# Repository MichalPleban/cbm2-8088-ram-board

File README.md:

# CBM-II 8088 CPU + RAM expansion board

## About the project

This repository is the hardware part of the project to create a PC compatibility system for Commodore CBM-II computers. The software counterpart is located at:

https://github.com/MichalPleban/cbm2-pc-emulator

More information about the project can be found at:

http://www.cbm-ii.com/

## About the board

The board is a replica of the original 8088 processor board for Commodore CBM-II computers. The replica is 100% compatible with the original card, so you can still run original MS-DOS 1.25 or CP/M-86 1.1 on it.

Several additional features were added to the card which allow for building a system that has enough power to run modern versions of DOS and DOS software:

### Fixed stability problems

The original card has serious stability problems in many machines, and it simply refuses to run on most low-profile CBM-II computers. These problems are caused by noise on /ERAS and /ECAS signals which cause memory corruption. Depending on the computer motherboard and/or PLA, the card may either work without any problems, hang once every few minutes or simply not work at all.

These problems are removed in the replica, and it works in all CBM-II computers.

### 1 MB memory expansion

The expanded memory is visible to both CPUs and allows DOS to access full 640 kB of memory – running DOS in only 256 kB leaves too little room for almost any application. The 64 kB segments above the 640 kB barrier can be individually turned off to allow other hardware (such as ISA graphics cards) to map into the address space.

The card has also the cartridge ROM with “fast boot” KERNAL modifications, thanks to which the memory test during powerup is greatly shortened (the test of 1 MB memory with the original would take around 2 minutes – this is shortened to mere 4 seconds).

### 12 MHz system clock

The card is equipped with a clock generator that produces either 12 MHz system clock with 50% duty cycle (for the NEC V20 processor) or 8 MHz clock with 33% duty cycle (for the 8088 processor). Compared with the 5 MHz on the original card, it gives a much faster system.
The system speed is further increased by using SRAM chips, which do not require refresh. Therefore the memory refresh system does not steal cycles from the CPU like on the original card.

### Hardware SPI interface

The SPI system is used to create a fast interface to a SD card, which serves as a 8 GB hard disk. Because the interface is implemented in hardware using shift registers, in combination with the INS/OUTS instructions of the NEC V20 CPU, it allows for theoretical read and write speed exceeding 1 MB / s.

### Battery backed RTC clock

The clock keeps the date and time for DOS and has also a few bytes of battery backed NVRAM to hold persistent configuration data.

### Reprogrammable EEPROM

The PC compatibility software is stored in an EEPROM chip, which can be reprogrammed from the 8088 side. Thanks to this, The library can be upgraded just by putting a newer version on the SD card and running the upgrade program from within DOS.

Having the whole software in the EEPROM allows also for diskless boot – the whole software is loaded from ROM, not from the disk like with the original card.

### Expansion port

The expansion port contains all the CPU bus signals, which should make it possible to add an ISA interface in the future. A smaller port with just the SPI and I2C signals is also available for additional hardware expansions in the future.

### Support for hardware virtualization

The card can generate NMI signal whenever an I/O port is accessed by the 8088 CPU. The I/O port access and the value being written to it are stored in hardware latches, so that the NMI routine can determine which I/O port was accessed and perform appropriate actions to simulate the hardware.

A video memory access latch was also added, which holds information about which parts of the video buffer at segment 0B000h was modified. This information speeds up screen refresh, because only the modified parts are being refreshed.

### 8087 coprocessor compatibility
The original card had a bug, due to which using the 8087 FPU was not possible – the card would lock up when the FPU was inserted into its socket. This bug has been fixed in the replica.

### Unobtainable chips replaced

The original card uses the 6525 Tri-Port Interface chip which is impossible to obtain. It has been replaced by an 8255 chip.

### Cartridge ROM sockets
The card has sockets for cartridge ROM or RAM at $4000, $6000 and $C000 which allow using  existing cartridge images. If a cartridge ROM is present, the card boot menu allows selecting whether to boot into BASIC or start the cartridge.

## Building the card

The PCB of the board has 4 layers to make it smaller and fit into the small space inside the low-profile CBM-II machines. Check with your PCB factory if they can make a 4 layer PCB for you.

The board contains an Atmel ATF1508 CPLD chip. You need a suitable programmer, such as ATF15xx-DK2, to program the chip. The board has a JEDEC connector which can be used to connect to the programmer directly. Use the cobalt.jed file from the repository to program the chip.

There are two ROM images in the archive which are necessary for the card to work:
-	8088.bin – 27C512 chip image to be placed at U7D
-	6509.bin  - 27C64 chip image to be placed at U2C

There are also chargen_lp.bin and chargen_hp.bin images which can be used to replace the character ROM in your machine (correspondently for low-profile and high-profile machines). They contain an alternate character set with some characters that are useful when running DOS (such as the backspace character). The card must be configured to use this character set – press F10 after booting the card.

The freedos.zip archive contains an image of a bootable FreeDOS hard disk. Put this image onto an SD card that is at least 8 GB of size (there are several SD card imaging applications available, I am using Win32 Disk Imager). After writing the images, the SD card will be readable on your PC, so you can easily add other applications. Note that you must use this image to boot the 8088 card, because the SD card must be formatted with special geometry for the INT 13h functions in the 8088 BIOS.

The ROM image from the repository contains the current version of the PC compatibility library. If you want to update the library in the future, grab the upgrade.com file from the repository, put it on the SD card and run it in DOS – it will write the newest version to the EEPROM chip on the board.

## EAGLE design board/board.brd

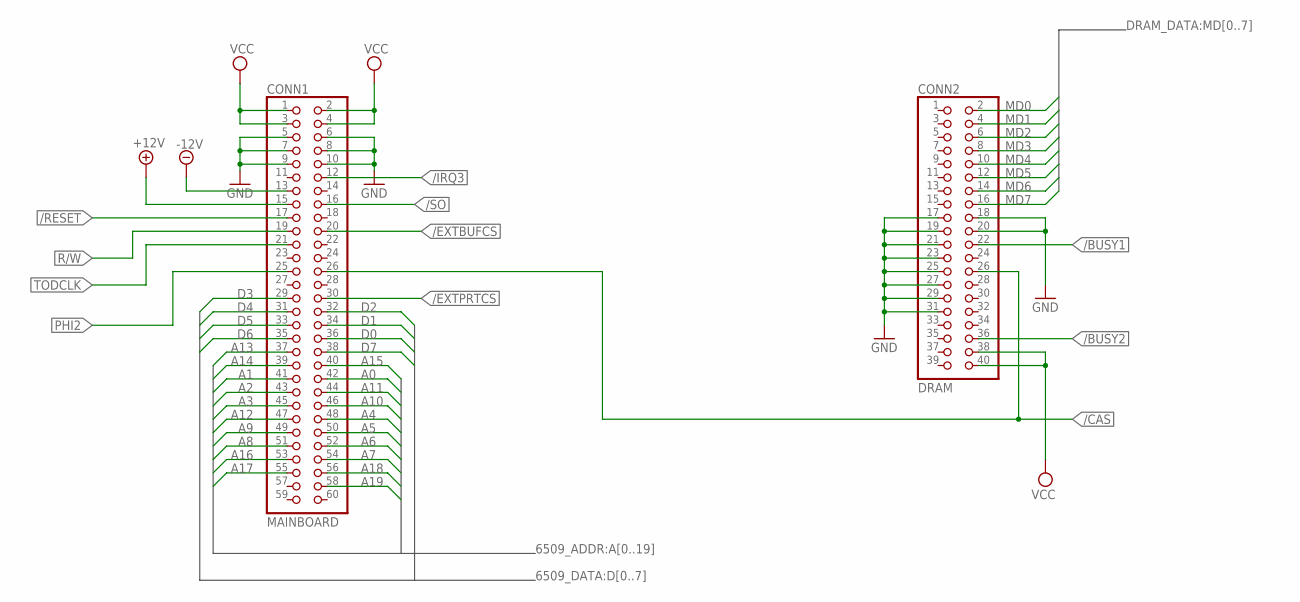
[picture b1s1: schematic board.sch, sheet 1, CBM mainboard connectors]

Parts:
CONN1: MAINBOARD; 2X30
CONN2: DRAM; 2X20

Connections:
+12V: CONN1.15; also elsewhere on the board
-12V: CONN1.13; also elsewhere on the board
/BUSY1: CONN2.22; also elsewhere on the board
/BUSY2: CONN2.36; also elsewhere on the board
/CAS: CONN1.26, CONN2.26; also elsewhere on the board
/EXTBUFCS: CONN1.20; also elsewhere on the board
/EXTPRTCS: CONN1.30; also elsewhere on the board
/IRQ3: CONN1.12; also elsewhere on the board
/RESET: CONN1.17; also elsewhere on the board
/SO: CONN1.16; also elsewhere on the board
A0: CONN1.42; also elsewhere on the board
A1: CONN1.41; also elsewhere on the board
A2: CONN1.43; also elsewhere on the board
A3: CONN1.45; also elsewhere on the board
A4: CONN1.48; also elsewhere on the board
A5: CONN1.50; also elsewhere on the board
A6: CONN1.52; also elsewhere on the board
A7: CONN1.54; also elsewhere on the board
A8: CONN1.51; also elsewhere on the board
A9: CONN1.49; also elsewhere on the board
A10: CONN1.46; also elsewhere on the board
A11: CONN1.44; also elsewhere on the board
A12: CONN1.47; also elsewhere on the board
A13: CONN1.37; also elsewhere on the board
A14: CONN1.39; also elsewhere on the board
A15: CONN1.40; also elsewhere on the board
A16: CONN1.53; also elsewhere on the board
A17: CONN1.55; also elsewhere on the board
A18: CONN1.56; also elsewhere on the board
A19: CONN1.58; also elsewhere on the board
D0: CONN1.36; also elsewhere on the board
D1: CONN1.34; also elsewhere on the board
D2: CONN1.32; also elsewhere on the board
D3: CONN1.29; also elsewhere on the board
D4: CONN1.31; also elsewhere on the board
D5: CONN1.33; also elsewhere on the board
D6: CONN1.35; also elsewhere on the board
D7: CONN1.38; also elsewhere on the board
GND: CONN1.5, CONN1.6, CONN1.7, CONN1.8, CONN1.9, CONN1.10, CONN2.17, CONN2.18, CONN2.19, CONN2.20, CONN2.21, CONN2.23, CONN2.25, CONN2.27, CONN2.29, CONN2.31; also elsewhere on the board
MD0: CONN2.2; also elsewhere on the board
MD1: CONN2.4; also elsewhere on the board
MD2: CONN2.6; also elsewhere on the board
MD3: CONN2.8; also elsewhere on the board
MD4: CONN2.10; also elsewhere on the board
MD5: CONN2.12; also elsewhere on the board
MD6: CONN2.14; also elsewhere on the board
MD7: CONN2.16; also elsewhere on the board
PHI2: CONN1.25; also elsewhere on the board
R/W: CONN1.19; also elsewhere on the board
TODCLK: CONN1.21; also elsewhere on the board
VCC: CONN1.1, CONN1.2, CONN1.3, CONN1.4, CONN2.38, CONN2.40; also elsewhere on the board

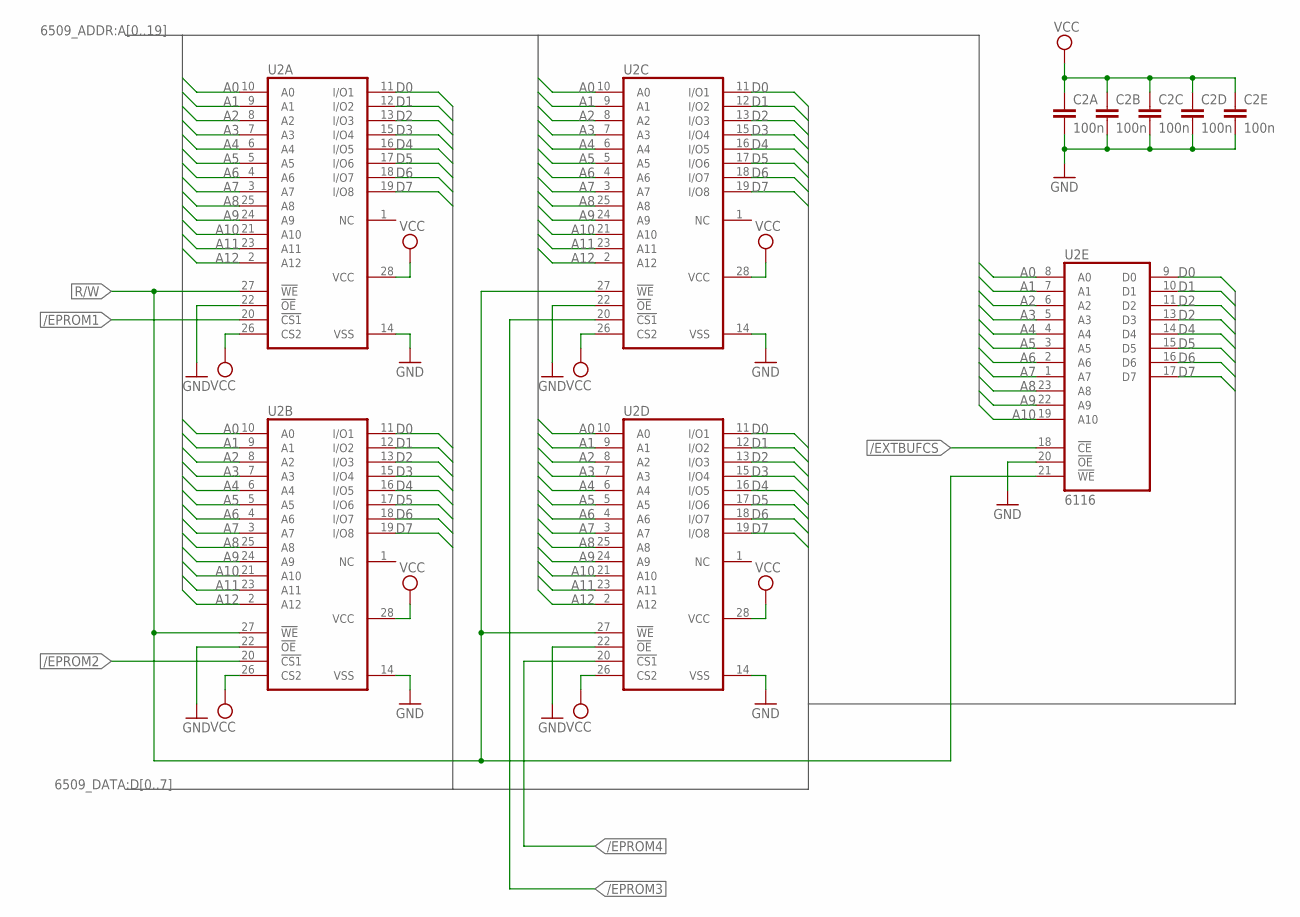
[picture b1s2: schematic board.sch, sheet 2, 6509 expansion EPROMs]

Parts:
C2A, C2B, C2C, C2D, C2E: 100n; C050-025X075
U2A, U2B, U2C, U2D: 6264A; DIL28-6
U2E: 6116; DIL24

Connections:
/EPROM1: U2A.20 (!CS1); also elsewhere on the board
/EPROM2: U2B.20 (!CS1); also elsewhere on the board
/EPROM3: U2C.20 (!CS1); also elsewhere on the board
/EPROM4: U2D.20 (!CS1); also elsewhere on the board
/EXTBUFCS: U2E.18 (!CE); also elsewhere on the board
A0: U2A.10 (A0), U2B.10 (A0), U2C.10 (A0), U2D.10 (A0), U2E.8 (A0); also elsewhere on the board
A1: U2A.9 (A1), U2B.9 (A1), U2C.9 (A1), U2D.9 (A1), U2E.7 (A1); also elsewhere on the board
A2: U2A.8 (A2), U2B.8 (A2), U2C.8 (A2), U2D.8 (A2), U2E.6 (A2); also elsewhere on the board
A3: U2A.7 (A3), U2B.7 (A3), U2C.7 (A3), U2D.7 (A3), U2E.5 (A3); also elsewhere on the board
A4: U2A.6 (A4), U2B.6 (A4), U2C.6 (A4), U2D.6 (A4), U2E.4 (A4); also elsewhere on the board
A5: U2A.5 (A5), U2B.5 (A5), U2C.5 (A5), U2D.5 (A5), U2E.3 (A5); also elsewhere on the board
A6: U2A.4 (A6), U2B.4 (A6), U2C.4 (A6), U2D.4 (A6), U2E.2 (A6); also elsewhere on the board
A7: U2A.3 (A7), U2B.3 (A7), U2C.3 (A7), U2D.3 (A7), U2E.1 (A7); also elsewhere on the board
A8: U2A.25 (A8), U2B.25 (A8), U2C.25 (A8), U2D.25 (A8), U2E.23 (A8); also elsewhere on the board
A9: U2A.24 (A9), U2B.24 (A9), U2C.24 (A9), U2D.24 (A9), U2E.22 (A9); also elsewhere on the board
A10: U2A.21 (A10), U2B.21 (A10), U2C.21 (A10), U2D.21 (A10), U2E.19 (A10); also elsewhere on the board
A11: U2A.23 (A11), U2B.23 (A11), U2C.23 (A11), U2D.23 (A11); also elsewhere on the board
A12: U2A.2 (A12), U2B.2 (A12), U2C.2 (A12), U2D.2 (A12); also elsewhere on the board
D0: U2A.11 (I/O1), U2B.11 (I/O1), U2C.11 (I/O1), U2D.11 (I/O1), U2E.9 (D0); also elsewhere on the board
D1: U2A.12 (I/O2), U2B.12 (I/O2), U2C.12 (I/O2), U2D.12 (I/O2), U2E.10 (D1); also elsewhere on the board
D2: U2A.13 (I/O3), U2B.13 (I/O3), U2C.13 (I/O3), U2D.13 (I/O3), U2E.11 (D2); also elsewhere on the board
D3: U2A.15 (I/O4), U2B.15 (I/O4), U2C.15 (I/O4), U2D.15 (I/O4), U2E.13 (D3); also elsewhere on the board
D4: U2A.16 (I/O5), U2B.16 (I/O5), U2C.16 (I/O5), U2D.16 (I/O5), U2E.14 (D4); also elsewhere on the board
D5: U2A.17 (I/O6), U2B.17 (I/O6), U2C.17 (I/O6), U2D.17 (I/O6), U2E.15 (D5); also elsewhere on the board
D6: U2A.18 (I/O7), U2B.18 (I/O7), U2C.18 (I/O7), U2D.18 (I/O7), U2E.16 (D6); also elsewhere on the board
D7: U2A.19 (I/O8), U2B.19 (I/O8), U2C.19 (I/O8), U2D.19 (I/O8), U2E.17 (D7); also elsewhere on the board
GND: C2A.2, C2B.2, C2C.2, C2D.2, C2E.2, U2A.14 (VSS), U2A.22 (!OE), U2B.14 (VSS), U2B.22 (!OE), U2C.14 (VSS), U2C.22 (!OE), U2D.14 (VSS), U2D.22 (!OE), U2E.12 (GND), U2E.20 (!OE); also elsewhere on the board
R/W: U2A.27 (!WE), U2B.27 (!WE), U2C.27 (!WE), U2D.27 (!WE), U2E.21 (!WE); also elsewhere on the board
VCC: C2A.1, C2B.1, C2C.1, C2D.1, C2E.1, U2A.26 (CS2), U2A.28 (VCC), U2B.26 (CS2), U2B.28 (VCC), U2C.26 (CS2), U2C.28 (VCC), U2D.26 (CS2), U2D.28 (VCC), U2E.24 (VCC); also elsewhere on the board

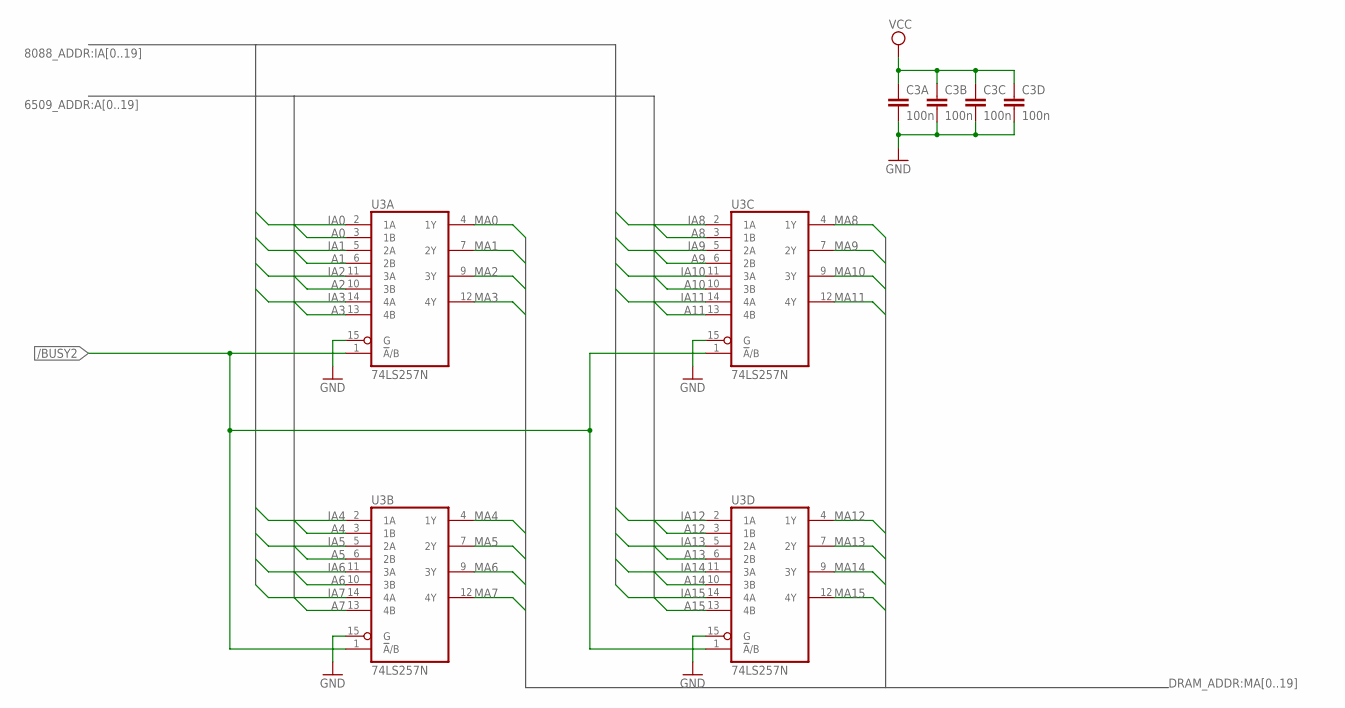
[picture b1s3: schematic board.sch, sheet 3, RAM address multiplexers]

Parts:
C3A, C3B, C3C, C3D: 100n; C050-025X075
U3A, U3B, U3C, U3D: 74LS257N; DIL16

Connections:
/BUSY2: U3A.1 (!A!/B), U3B.1 (!A!/B), U3C.1 (!A!/B), U3D.1 (!A!/B); also elsewhere on the board
A0: U3A.3 (1B); also elsewhere on the board
A1: U3A.6 (2B); also elsewhere on the board
A2: U3A.10 (3B); also elsewhere on the board
A3: U3A.13 (4B); also elsewhere on the board
A4: U3B.3 (1B); also elsewhere on the board
A5: U3B.6 (2B); also elsewhere on the board
A6: U3B.10 (3B); also elsewhere on the board
A7: U3B.13 (4B); also elsewhere on the board
A8: U3C.3 (1B); also elsewhere on the board
A9: U3C.6 (2B); also elsewhere on the board
A10: U3C.10 (3B); also elsewhere on the board
A11: U3C.13 (4B); also elsewhere on the board
A12: U3D.3 (1B); also elsewhere on the board
A13: U3D.6 (2B); also elsewhere on the board
A14: U3D.10 (3B); also elsewhere on the board
A15: U3D.13 (4B); also elsewhere on the board
GND: C3A.2, C3B.2, C3C.2, C3D.2, U3A.8 (GND), U3A.15 (G), U3B.8 (GND), U3B.15 (G), U3C.8 (GND), U3C.15 (G), U3D.8 (GND), U3D.15 (G); also elsewhere on the board
IA0: U3A.2 (1A); also elsewhere on the board
IA1: U3A.5 (2A); also elsewhere on the board
IA2: U3A.11 (3A); also elsewhere on the board
IA3: U3A.14 (4A); also elsewhere on the board
IA4: U3B.2 (1A); also elsewhere on the board
IA5: U3B.5 (2A); also elsewhere on the board
IA6: U3B.11 (3A); also elsewhere on the board
IA7: U3B.14 (4A); also elsewhere on the board
IA8: U3C.2 (1A); also elsewhere on the board
IA9: U3C.5 (2A); also elsewhere on the board
IA10: U3C.11 (3A); also elsewhere on the board
IA11: U3C.14 (4A); also elsewhere on the board
IA12: U3D.2 (1A); also elsewhere on the board
IA13: U3D.5 (2A); also elsewhere on the board
IA14: U3D.11 (3A); also elsewhere on the board
IA15: U3D.14 (4A); also elsewhere on the board
MA0: U3A.4 (1Y); also elsewhere on the board
MA1: U3A.7 (2Y); also elsewhere on the board
MA2: U3A.9 (3Y); also elsewhere on the board
MA3: U3A.12 (4Y); also elsewhere on the board
MA4: U3B.4 (1Y); also elsewhere on the board
MA5: U3B.7 (2Y); also elsewhere on the board
MA6: U3B.9 (3Y); also elsewhere on the board
MA7: U3B.12 (4Y); also elsewhere on the board
MA8: U3C.4 (1Y); also elsewhere on the board
MA9: U3C.7 (2Y); also elsewhere on the board
MA10: U3C.9 (3Y); also elsewhere on the board
MA11: U3C.12 (4Y); also elsewhere on the board
MA12: U3D.4 (1Y); also elsewhere on the board
MA13: U3D.7 (2Y); also elsewhere on the board
MA14: U3D.9 (3Y); also elsewhere on the board
MA15: U3D.12 (4Y); also elsewhere on the board
VCC: C3A.1, C3B.1, C3C.1, C3D.1, U3A.16 (VCC), U3B.16 (VCC), U3C.16 (VCC), U3D.16 (VCC); also elsewhere on the board

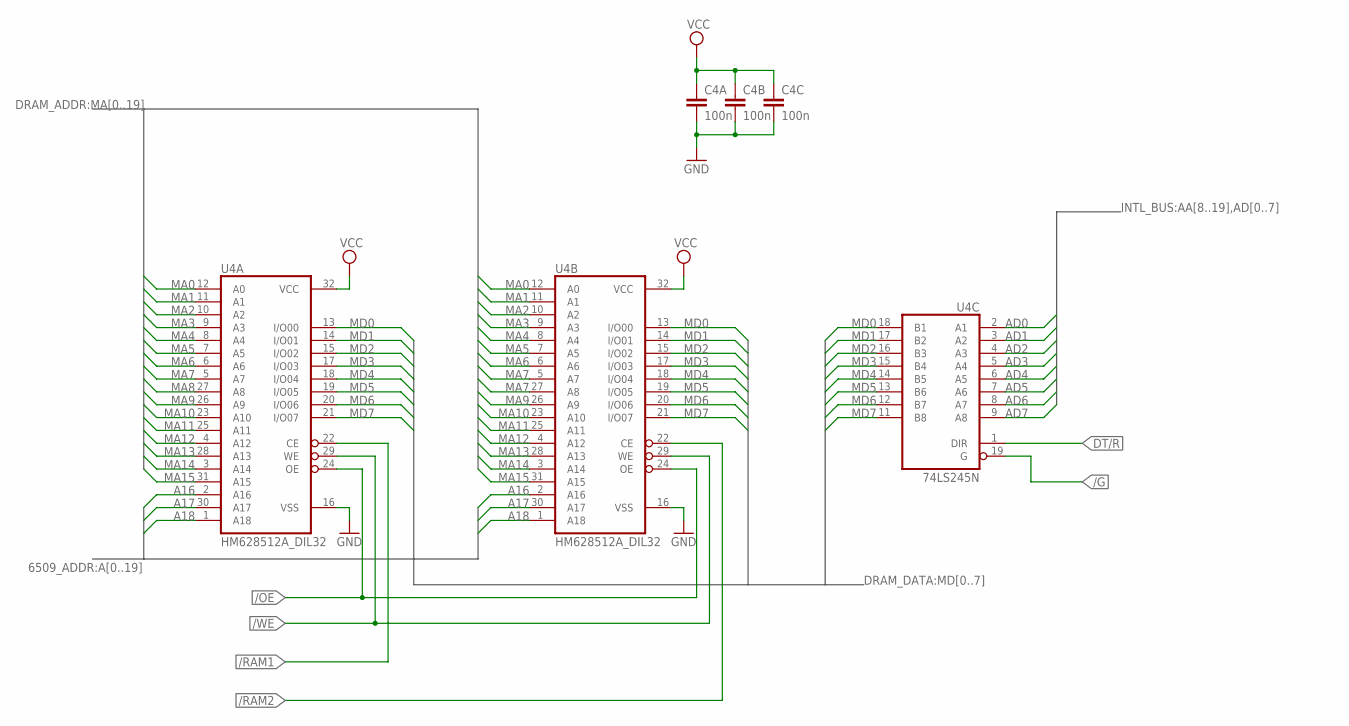
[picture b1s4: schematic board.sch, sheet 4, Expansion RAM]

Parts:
C4A, C4B, C4C: 100n; C050-025X075
U4A, U4B: HM628512A_DIL32; DIL32
U4C: 74LS245N; DIL20

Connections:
/G: U4C.19 (G); also elsewhere on the board
/OE: U4A.24 (OE), U4B.24 (OE); also elsewhere on the board
/RAM1: U4A.22 (CE); also elsewhere on the board
/RAM2: U4B.22 (CE); also elsewhere on the board
/WE: U4A.29 (WE), U4B.29 (WE); also elsewhere on the board
A16: U4A.2 (A16), U4B.2 (A16); also elsewhere on the board
A17: U4A.30 (A17), U4B.30 (A17); also elsewhere on the board
A18: U4A.1 (A18), U4B.1 (A18); also elsewhere on the board
AD0: U4C.2 (A1); also elsewhere on the board
AD1: U4C.3 (A2); also elsewhere on the board
AD2: U4C.4 (A3); also elsewhere on the board
AD3: U4C.5 (A4); also elsewhere on the board
AD4: U4C.6 (A5); also elsewhere on the board
AD5: U4C.7 (A6); also elsewhere on the board
AD6: U4C.8 (A7); also elsewhere on the board
AD7: U4C.9 (A8); also elsewhere on the board
DT/R: U4C.1 (DIR); also elsewhere on the board
GND: C4A.2, C4B.2, C4C.2, U4A.16 (VSS), U4B.16 (VSS), U4C.10 (GND); also elsewhere on the board
MA0: U4A.12 (A0), U4B.12 (A0); also elsewhere on the board
MA1: U4A.11 (A1), U4B.11 (A1); also elsewhere on the board
MA2: U4A.10 (A2), U4B.10 (A2); also elsewhere on the board
MA3: U4A.9 (A3), U4B.9 (A3); also elsewhere on the board
MA4: U4A.8 (A4), U4B.8 (A4); also elsewhere on the board
MA5: U4A.7 (A5), U4B.7 (A5); also elsewhere on the board
MA6: U4A.6 (A6), U4B.6 (A6); also elsewhere on the board
MA7: U4A.5 (A7), U4B.5 (A7); also elsewhere on the board
MA8: U4A.27 (A8), U4B.27 (A8); also elsewhere on the board
MA9: U4A.26 (A9), U4B.26 (A9); also elsewhere on the board
MA10: U4A.23 (A10), U4B.23 (A10); also elsewhere on the board
MA11: U4A.25 (A11), U4B.25 (A11); also elsewhere on the board
MA12: U4A.4 (A12), U4B.4 (A12); also elsewhere on the board
MA13: U4A.28 (A13), U4B.28 (A13); also elsewhere on the board
MA14: U4A.3 (A14), U4B.3 (A14); also elsewhere on the board
MA15: U4A.31 (A15), U4B.31 (A15); also elsewhere on the board
MD0: U4A.13 (I/O00), U4B.13 (I/O00), U4C.18 (B1); also elsewhere on the board
MD1: U4A.14 (I/O01), U4B.14 (I/O01), U4C.17 (B2); also elsewhere on the board
MD2: U4A.15 (I/O02), U4B.15 (I/O02), U4C.16 (B3); also elsewhere on the board
MD3: U4A.17 (I/O03), U4B.17 (I/O03), U4C.15 (B4); also elsewhere on the board
MD4: U4A.18 (I/O04), U4B.18 (I/O04), U4C.14 (B5); also elsewhere on the board
MD5: U4A.19 (I/O05), U4B.19 (I/O05), U4C.13 (B6); also elsewhere on the board
MD6: U4A.20 (I/O06), U4B.20 (I/O06), U4C.12 (B7); also elsewhere on the board
MD7: U4A.21 (I/O07), U4B.21 (I/O07), U4C.11 (B8); also elsewhere on the board
VCC: C4A.1, C4B.1, C4C.1, U4A.32 (VCC), U4B.32 (VCC), U4C.20 (VCC); also elsewhere on the board

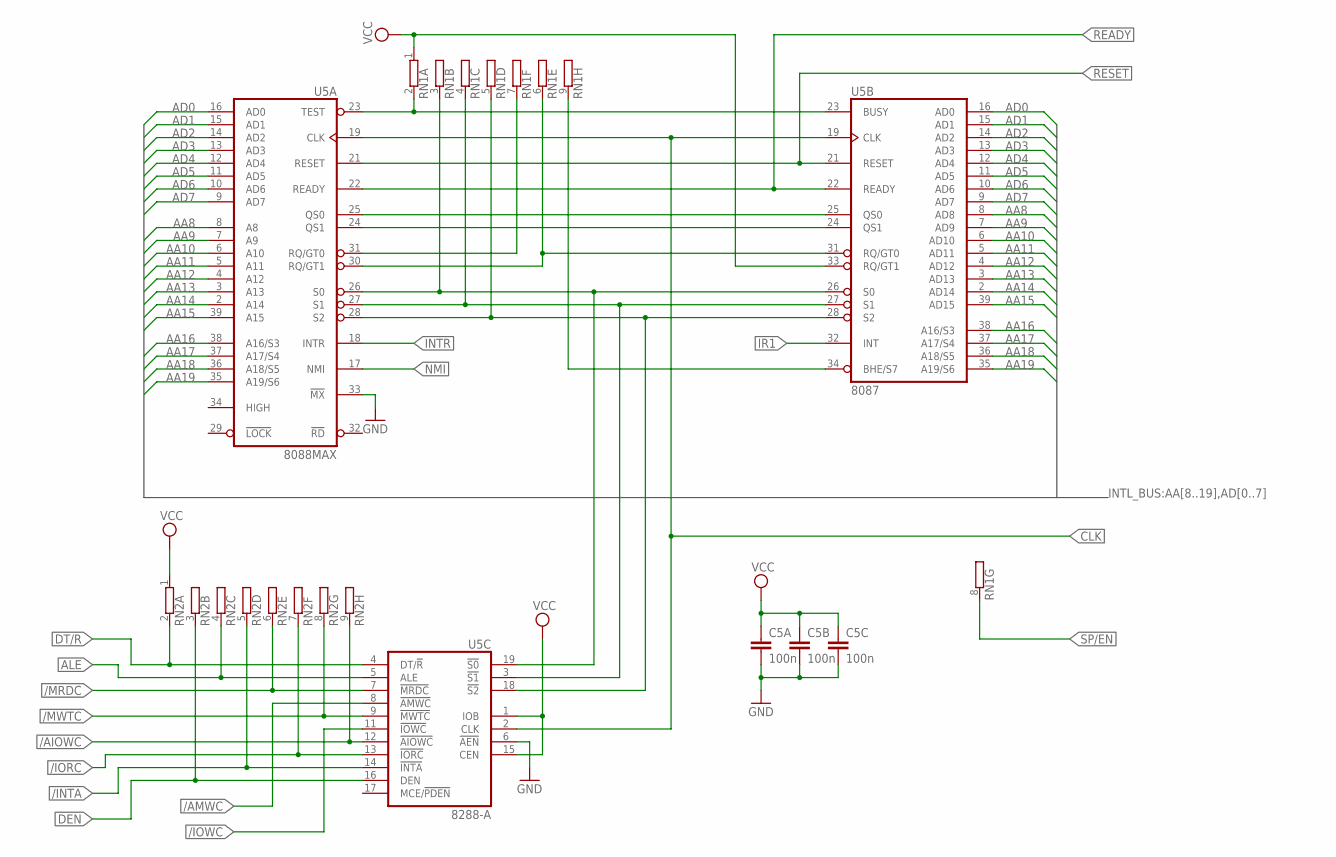
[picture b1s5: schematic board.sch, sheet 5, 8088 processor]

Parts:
C5A, C5B, C5C: 100n; C050-025X075
RN1, RN2: GE08R; SIL9
U5A: 8088MAX; DIL40
U5B: 8087; DIL40
U5C: 8288-A; DIL20

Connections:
/AIOWC: RN2.9 (2), U5C.12 (!AIOWC); also elsewhere on the board
/AMWC: U5C.8 (!AMWC); also elsewhere on the board
/INTA: RN2.5 (2), U5C.14 (!INTA); also elsewhere on the board
/IORC: RN2.7 (2), U5C.13 (!IORC); also elsewhere on the board
/IOWC: U5C.11 (!IOWC); also elsewhere on the board
/MRDC: RN2.6 (2), U5C.7 (!MRDC); also elsewhere on the board
/MWTC: RN2.8 (2), U5C.9 (!MWTC); also elsewhere on the board
/TEST: RN1.2, U5A.23 (TEST), U5B.23 (BUSY)
AA8: U5A.8 (A8), U5B.8 (AD8); also elsewhere on the board
AA9: U5A.7 (A9), U5B.7 (AD9); also elsewhere on the board
AA10: U5A.6 (A10), U5B.6 (AD10); also elsewhere on the board
AA11: U5A.5 (A11), U5B.5 (AD11); also elsewhere on the board
AA12: U5A.4 (A12), U5B.4 (AD12); also elsewhere on the board
AA13: U5A.3 (A13), U5B.3 (AD13); also elsewhere on the board
AA14: U5A.2 (A14), U5B.2 (AD14); also elsewhere on the board
AA15: U5A.39 (A15), U5B.39 (AD15); also elsewhere on the board
AA16: U5A.38 (A16/S3), U5B.38 (A16/S3); also elsewhere on the board
AA17: U5A.37 (A17/S4), U5B.37 (A17/S4); also elsewhere on the board
AA18: U5A.36 (A18/S5), U5B.36 (A18/S5); also elsewhere on the board
AA19: U5A.35 (A19/S6), U5B.35 (A19/S6); also elsewhere on the board
AD0: U5A.16 (AD0), U5B.16 (AD0); also elsewhere on the board
AD1: U5A.15 (AD1), U5B.15 (AD1); also elsewhere on the board
AD2: U5A.14 (AD2), U5B.14 (AD2); also elsewhere on the board
AD3: U5A.13 (AD3), U5B.13 (AD3); also elsewhere on the board
AD4: U5A.12 (AD4), U5B.12 (AD4); also elsewhere on the board
AD5: U5A.11 (AD5), U5B.11 (AD5); also elsewhere on the board
AD6: U5A.10 (AD6), U5B.10 (AD6); also elsewhere on the board
AD7: U5A.9 (AD7), U5B.9 (AD7); also elsewhere on the board
ALE: RN2.4 (2), U5C.5 (ALE); also elsewhere on the board
BHE/S7: RN1.9 (2), U5B.34 (BHE/S7)
CLK: U5A.19 (CLK), U5B.19 (CLK), U5C.2 (CLK); also elsewhere on the board
DEN: RN2.3 (2), U5C.16 (DEN); also elsewhere on the board
DT/R: RN2.2, U5C.4 (DT/!R); also elsewhere on the board
GND: C5A.2, C5B.2, C5C.2, U5A.1 (GND), U5A.20 (GND), U5A.33 (!MX), U5B.1 (GND), U5B.20 (GND), U5C.6 (!AEN), U5C.10 (GND); also elsewhere on the board
INTR: U5A.18 (INTR); also elsewhere on the board
IR1: U5B.32 (INT); also elsewhere on the board
NMI: U5A.17 (NMI); also elsewhere on the board
QS0: U5A.25 (QS0), U5B.25 (QS0)
QS1: U5A.24 (QS1), U5B.24 (QS1)
READY: U5A.22 (READY), U5B.22 (READY); also elsewhere on the board
RESET: U5A.21 (RESET), U5B.21 (RESET); also elsewhere on the board
RQ: RN1.7 (2), U5A.31 (RQ/GT0)
RQ/GT0: RN1.6 (2), U5A.30 (RQ/GT1), U5B.31 (RQ/GT0)
S0: RN1.3 (2), U5A.26 (S0), U5B.26 (S0), U5C.19 (!S0)
S1: RN1.4 (2), U5A.27 (S1), U5B.27 (S1), U5C.3 (!S1)
S2: RN1.5 (2), U5A.28 (S2), U5B.28 (S2), U5C.18 (!S2)
SP/EN: RN1.8 (2); also elsewhere on the board
VCC: C5A.1, C5B.1, C5C.1, RN1.1, RN2.1, U5A.40 (VCC), U5B.33 (RQ/GT1), U5B.40 (VCC), U5C.1 (IOB), U5C.15 (CEN), U5C.20 (VCC); also elsewhere on the board

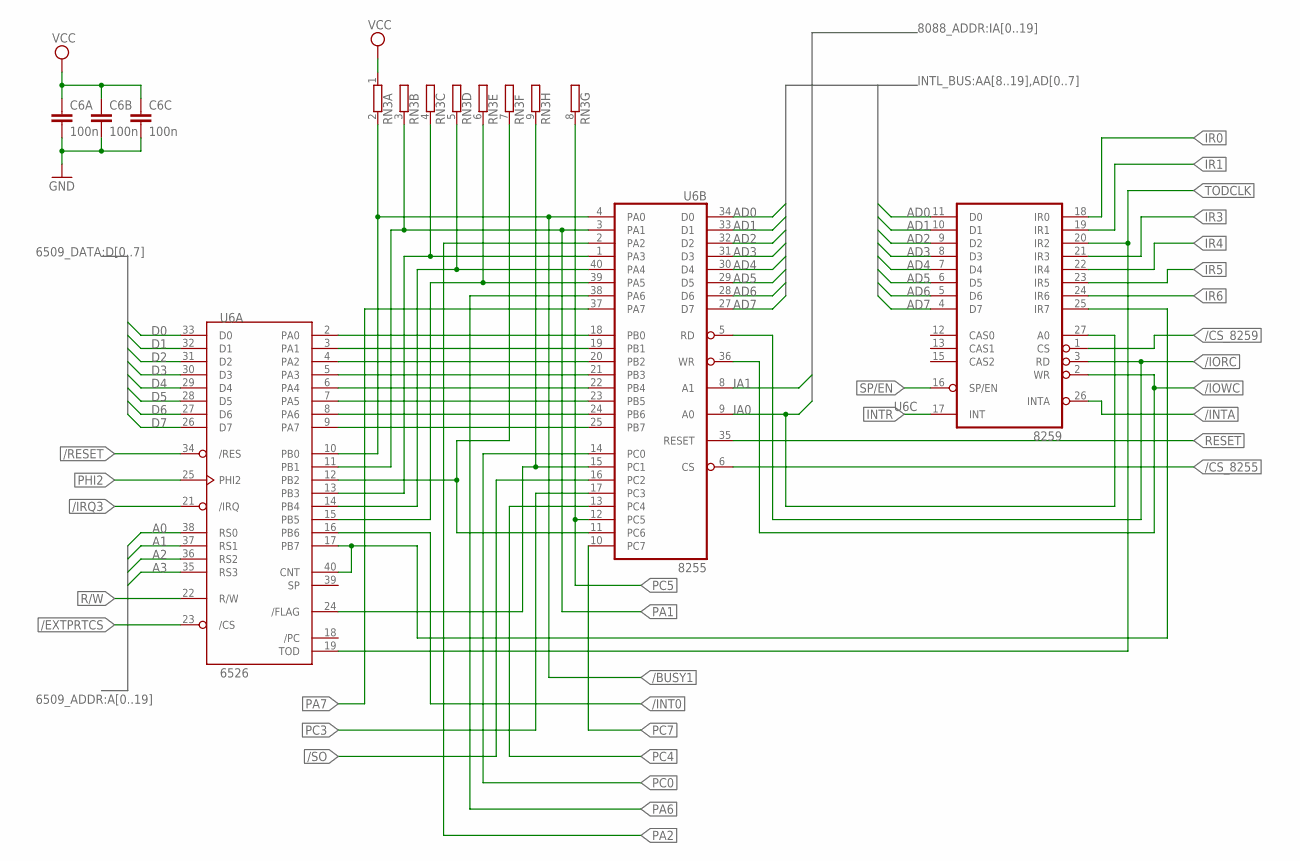
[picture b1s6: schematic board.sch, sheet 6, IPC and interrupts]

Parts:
C6A, C6B, C6C: 100n; C050-025X075
RN3: GE08R; SIL9
U6A: 6526; DIP40
U6B: 8255; DIL40
U6C: 8259; DIL28-6

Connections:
/BUSY1: RN3.2, U6A.10 (PB0), U6B.4 (PA0); also elsewhere on the board
/CS_8255: U6B.6 (CS); also elsewhere on the board
/CS_8259: U6C.1 (CS); also elsewhere on the board
/EXTPRTCS: U6A.23 (/CS); also elsewhere on the board
/INT0: U6A.16 (PB6); also elsewhere on the board
/INTA: U6C.26 (INTA); also elsewhere on the board
/IORC: U6B.5 (RD), U6C.3 (RD); also elsewhere on the board
/IOWC: U6B.36 (WR), U6C.2 (WR); also elsewhere on the board
/IRQ3: U6A.21 (/IRQ); also elsewhere on the board
/RESET: U6A.34 (/RES); also elsewhere on the board
/SO: U6B.16 (PC2); also elsewhere on the board
A0: U6A.38 (RS0); also elsewhere on the board
A1: U6A.37 (RS1); also elsewhere on the board
A2: U6A.36 (RS2); also elsewhere on the board
A3: U6A.35 (RS3); also elsewhere on the board
AD0: U6B.34 (D0), U6C.11 (D0); also elsewhere on the board
AD1: U6B.33 (D1), U6C.10 (D1); also elsewhere on the board
AD2: U6B.32 (D2), U6C.9 (D2); also elsewhere on the board
AD3: U6B.31 (D3), U6C.8 (D3); also elsewhere on the board
AD4: U6B.30 (D4), U6C.7 (D4); also elsewhere on the board
AD5: U6B.29 (D5), U6C.6 (D5); also elsewhere on the board
AD6: U6B.28 (D6), U6C.5 (D6); also elsewhere on the board
AD7: U6B.27 (D7), U6C.4 (D7); also elsewhere on the board
D0: U6A.33 (D0); also elsewhere on the board
D1: U6A.32 (D1); also elsewhere on the board
D2: U6A.31 (D2); also elsewhere on the board
D3: U6A.30 (D3); also elsewhere on the board
D4: U6A.29 (D4); also elsewhere on the board
D5: U6A.28 (D5); also elsewhere on the board
D6: U6A.27 (D6); also elsewhere on the board
D7: U6A.26 (D7); also elsewhere on the board
GND: C6A.2, C6B.2, C6C.2, U6A.1 (GND), U6B.7 (GND), U6C.14 (GND); also elsewhere on the board
IA0: U6B.9 (A0), U6C.27 (A0); also elsewhere on the board
IA1: U6B.8 (A1); also elsewhere on the board
INTR: U6C.17 (INT); also elsewhere on the board
IR0: U6C.18 (IR0); also elsewhere on the board
IR1: U6C.19 (IR1); also elsewhere on the board
IR3: U6C.21 (IR3); also elsewhere on the board
IR4: U6C.22 (IR4); also elsewhere on the board
IR5: U6C.23 (IR5); also elsewhere on the board
IR6: U6C.24 (IR6); also elsewhere on the board
IR7: U6A.17 (PB7), U6A.40 (CNT), U6C.25 (IR7)
PA1: RN3.3 (2), U6A.11 (PB1), U6B.3 (PA1); also elsewhere on the board
PA2: U6B.2 (PA2); also elsewhere on the board
PA3: RN3.4 (2), U6A.13 (PB3), U6B.1 (PA3)
PA4: RN3.5 (2), U6A.14 (PB4), U6B.40 (PA4)
PA5: RN3.6 (2), U6A.15 (PB5), U6B.39 (PA5)
PA6: U6B.38 (PA6); also elsewhere on the board
PA7: U6B.37 (PA7); also elsewhere on the board
PB0: U6A.2 (PA0), U6B.18 (PB0)
PB1: U6A.3 (PA1), U6B.19 (PB1)
PB2: U6A.4 (PA2), U6B.20 (PB2)
PB3: U6A.5 (PA3), U6B.21 (PB3)
PB4: U6A.6 (PA4), U6B.22 (PB4)
PB5: U6A.7 (PA5), U6B.23 (PB5)
PB6: U6A.8 (PA6), U6B.24 (PB6)
PB7: U6A.9 (PA7), U6B.25 (PB7)
PC0: U6B.14 (PC0); also elsewhere on the board
PC1: RN3.9 (2), U6A.24 (/FLAG), U6B.15 (PC1)
PC3: U6B.17 (PC3); also elsewhere on the board
PC4: U6B.13 (PC4); also elsewhere on the board
PC5: RN3.8 (2), U6B.12 (PC5); also elsewhere on the board
PC6: RN3.7 (2), U6A.12 (PB2), U6B.11 (PC6)
PC7: U6B.10 (PC7); also elsewhere on the board
PHI2: U6A.25 (PHI2); also elsewhere on the board
R/W: U6A.22 (R/W); also elsewhere on the board
RESET: U6B.35 (RESET); also elsewhere on the board
SP/EN: U6C.16 (SP/EN); also elsewhere on the board
TODCLK: U6A.19 (TOD), U6C.20 (IR2); also elsewhere on the board
VCC: C6A.1, C6B.1, C6C.1, RN3.1, U6A.20 (VCC), U6B.26 (VCC), U6C.28 (VCC); also elsewhere on the board

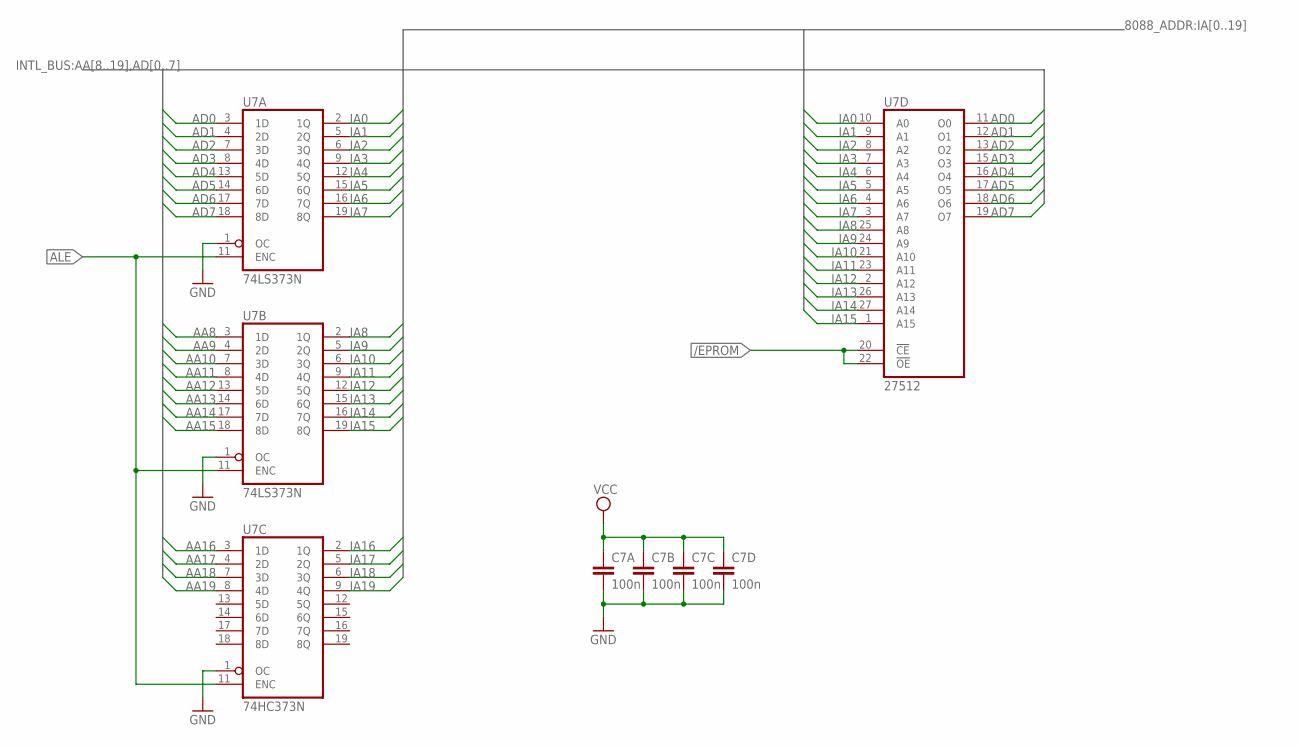
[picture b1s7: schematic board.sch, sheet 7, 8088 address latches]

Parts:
C7A, C7B, C7C, C7D: 100n; C050-025X075
U7A, U7B: 74LS373N; DIL20
U7C: 74HC373N; DIL20
U7D: 27512; DIL28

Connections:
/EPROM: U7D.20 (!CE), U7D.22 (!OE); also elsewhere on the board
AA8: U7B.3 (1D); also elsewhere on the board
AA9: U7B.4 (2D); also elsewhere on the board
AA10: U7B.7 (3D); also elsewhere on the board
AA11: U7B.8 (4D); also elsewhere on the board
AA12: U7B.13 (5D); also elsewhere on the board
AA13: U7B.14 (6D); also elsewhere on the board
AA14: U7B.17 (7D); also elsewhere on the board
AA15: U7B.18 (8D); also elsewhere on the board
AA16: U7C.3 (1D); also elsewhere on the board
AA17: U7C.4 (2D); also elsewhere on the board
AA18: U7C.7 (3D); also elsewhere on the board
AA19: U7C.8 (4D); also elsewhere on the board
AD0: U7A.3 (1D), U7D.11 (O0); also elsewhere on the board
AD1: U7A.4 (2D), U7D.12 (O1); also elsewhere on the board
AD2: U7A.7 (3D), U7D.13 (O2); also elsewhere on the board
AD3: U7A.8 (4D), U7D.15 (O3); also elsewhere on the board
AD4: U7A.13 (5D), U7D.16 (O4); also elsewhere on the board
AD5: U7A.14 (6D), U7D.17 (O5); also elsewhere on the board
AD6: U7A.17 (7D), U7D.18 (O6); also elsewhere on the board
AD7: U7A.18 (8D), U7D.19 (O7); also elsewhere on the board
ALE: U7A.11 (ENC), U7B.11 (ENC), U7C.11 (ENC); also elsewhere on the board
GND: C7A.2, C7B.2, C7C.2, C7D.2, U7A.1 (OC), U7A.10 (GND), U7B.1 (OC), U7B.10 (GND), U7C.1 (OC), U7C.10 (GND), U7D.14 (GND); also elsewhere on the board
IA0: U7A.2 (1Q), U7D.10 (A0); also elsewhere on the board
IA1: U7A.5 (2Q), U7D.9 (A1); also elsewhere on the board
IA2: U7A.6 (3Q), U7D.8 (A2); also elsewhere on the board
IA3: U7A.9 (4Q), U7D.7 (A3); also elsewhere on the board
IA4: U7A.12 (5Q), U7D.6 (A4); also elsewhere on the board
IA5: U7A.15 (6Q), U7D.5 (A5); also elsewhere on the board
IA6: U7A.16 (7Q), U7D.4 (A6); also elsewhere on the board
IA7: U7A.19 (8Q), U7D.3 (A7); also elsewhere on the board
IA8: U7B.2 (1Q), U7D.25 (A8); also elsewhere on the board
IA9: U7B.5 (2Q), U7D.24 (A9); also elsewhere on the board
IA10: U7B.6 (3Q), U7D.21 (A10); also elsewhere on the board
IA11: U7B.9 (4Q), U7D.23 (A11); also elsewhere on the board
IA12: U7B.12 (5Q), U7D.2 (A12); also elsewhere on the board
IA13: U7B.15 (6Q), U7D.26 (A13); also elsewhere on the board
IA14: U7B.16 (7Q), U7D.27 (A14); also elsewhere on the board
IA15: U7B.19 (8Q), U7D.1 (A15); also elsewhere on the board
IA16: U7C.2 (1Q); also elsewhere on the board
IA17: U7C.5 (2Q); also elsewhere on the board
IA18: U7C.6 (3Q); also elsewhere on the board
IA19: U7C.9 (4Q); also elsewhere on the board
VCC: C7A.1, C7B.1, C7C.1, C7D.1, U7A.20 (VCC), U7B.20 (VCC), U7C.20 (VCC), U7D.28 (VCC); also elsewhere on the board

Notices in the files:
board/board.brd:
(C) 2020 Michal Pleban
